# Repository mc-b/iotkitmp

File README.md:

ESP32 DevKitC und IoTKitV3
==========================

| ESP32 DevKitC | IoTKitV3 Shield |
| ---------- | ------ |
|  |  |
| Quelle: [Micropython](https://docs.micropython.org/en/latest/esp32/quickref.html) | Quelle: [IoTKitV3](https://github.com/iotkitv3/intro) |

Beispiele für das [ESP32 DevKitC](https://docs.espressif.com/projects/esp-idf/en/latest/esp32/hw-reference/esp32/get-started-devkitc.html) Board in Kombination mit dem [IoTKit V3 Shield](https://github.com/iotkitv3/iotkit#iotkit-v3-shield-small).

Dieses Repository basiert auf den Erfahrungen mit dem [IoTKitV1 - V3](https://github.com/iotkitv3/intro).

## Grundlagen

* [Hardware](hw/)
* [Software und Installation](sw/)
* [GPIO](gpio)
* [Sensoren](sensors)
* [Aktoren](actors)

## Bus Systeme

* [UART](uart)
* [I²C/TWI](i2c)
* [SPI](spi)

### Internet IoT Protokolle

* [WLAN](wlan/) inkl. Konfiguration SSID und WLAN Password.
* [HTTP und REST](http/) 
* [MQTT](mqtt/)

## Anwendungen / Umsetzungen

* [NFC / RFID](rfid/)
* [Cloud Anbindung](cloud/) an Amazon (AWS) und Microsoft (Azure).
* [Internet of Things – Machine Learning Fast Data Pipeline mit Docker/Kubernetes](pipeline/)

## Kurse und Weiterbildung 

* [CAS Internet of Things (IoT) and Digital Ecosystem Technologien verstehen, Lösungen entwickeln](http://hslu.ch/casiot)
* [CAS Cloud and Platform Manager Mit Cloud-Expertise die Digitalisierung mitgestalten](http://hslu.ch/cascpm) 
* [Internet of Things (IoT) im Einsatz](https://www.digicomp.ch/d/IOTEIN)

## Links

* [Die drei Hauptklassen von IoT](https://www.arm.com/products/iot/soc)
* [Geschäftsmodelle und IoT](https://www.iot-lab.ch/publications/#whitepapers)

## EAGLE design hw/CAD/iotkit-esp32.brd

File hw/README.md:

ESP32-DevKitC
-------------
***

> [⇧ **Home**](../README.md)

- - -

* 32-Bit-MCU und 2,4-GHz-WLAN und Bluetooth/Bluetooth LE
* Eingebetteter ESP32, zwei oder ein Xtensa® 32-Bit-LX6-Mikroprozessor(en) mit einstellbarer Taktfrequenz von 80 MHz bis 240 MHz
* +19,5 dBm Ausgangsleistung sorgen für eine gute physikalische Reichweite
* Klassisches Bluetooth für Legacy-Verbindungen, unterstützt auch L2CAP, SDP, GAP, SMP, AVDTP, AVCTP, A2DP (SNK) und AVRCP (CT)
* Unterstützung für Bluetooth Low Energy (Bluetooth LE)-Profile einschließlich L2CAP, GAP, GATT, SMP und GATT-basierte Profile wie BluFi, SPP-like usw
* Bluetooth Low Energy (Bluetooth LE) stellt eine Verbindung zu Smartphones her und sendet Niedrigenergie-Beacons zur einfachen Erkennung
* Der Ruhestrom beträgt weniger als 5 μA und eignet sich daher für batteriebetriebene und tragbare Elektronikanwendungen
* Zu den Peripheriegeräten gehören kapazitive Berührungssensoren, Hall-Sensor, SD-Kartenschnittstelle, Ethernet, Hochgeschwindigkeits-SPI, UART, I2S und I2C
* Vollständig zertifiziert mit integrierter Antenne und Software-Stacks

### Pins

* 22 Pins In/Out
*  4 Pins nur Input (34, 35, 36, 39)
* max. 8 PWM Channels gleichzeitig

### Links

* [Hersteller](https://www.espressif.com/en/products/modules)
* [Board](https://www.mouser.ch/ProductDetail/356-ESP32-DEVKTC32VE)
* [Firmware](https://micropython.org/download/esp32/) - Version V1.14 verwenden, V1.18 funktioniert PWM nicht.

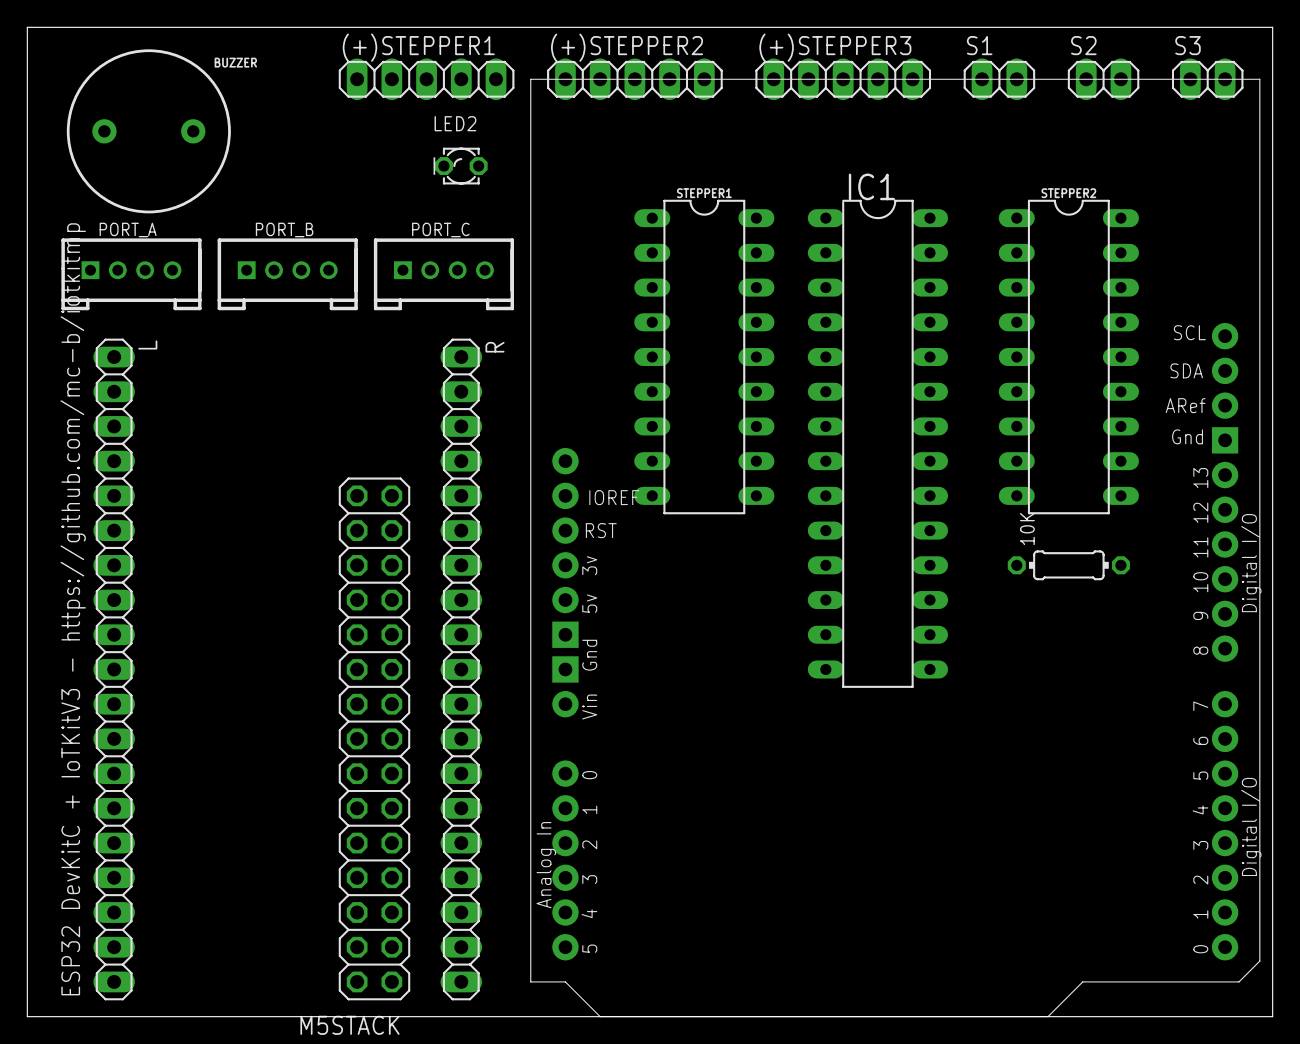
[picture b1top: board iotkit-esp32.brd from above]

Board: 2 copper layers, 91.1 x 72.4 mm, 19 parts (0 on the bottom side), 53 nets, no tracks yet.

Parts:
10K: 0204/7
(+)STEPPER1: PB0-3; 1X05
(+)STEPPER2: PB4-7; 1X05
(+)STEPPER3: PA7-4; 1X05
BUZZER: BUZZER-PTH; BUZZER-12MM
IC1: MCP23017SP 0x20; DIL28-3
L: 1X19
LED2: LED_LD260
M5STACK: 2X15
PORT_A: I2C; HW4-2.0
PORT_B: I2C; HW4-2.0
PORT_C: I2C; HW4-2.0
R: 1X19
S1: PA0; 1X02
S2: PA1; 1X02
S3: PA2; 1X02
STEPPER1, STEPPER2: DIL18
U$1: ARDUINO_LEONARDO

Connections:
3V3: 10K.1, IC1.9, L.1, M5STACK.11, U$1.3V
5V: (+)STEPPER1.1, (+)STEPPER2.1, (+)STEPPER3.1, L.19, M5STACK.27, PORT_A.3, PORT_B.3, PORT_C.3, STEPPER1.10, STEPPER2.10, U$1.5V
A2: L.7, M5STACK.1, U$1.A2
A3: L.8, M5STACK.3, U$1.A3
A4: L.5, M5STACK.13, U$1.A4
A5: L.6, M5STACK.14, U$1.A5
BUZ: BUZZER.+, L.10
D0: M5STACK.16, PORT_C.1, R.5, U$1.D0
D1: M5STACK.15, PORT_C.2, R.4, U$1.D1
D2: L.13, M5STACK.24, U$1.D2
D3: L.15, M5STACK.21, U$1.D3
D4: L.12, M5STACK.23, U$1.D4
D5: R.16, U$1.D5
D6: R.12, U$1.D6
D7: R.11, U$1.D7
D8: M5STACK.9, PORT_B.2, R.9, U$1.D8
D9: M5STACK.22, PORT_B.1, R.8, U$1.D9
D10: L.11, M5STACK.7, U$1.D10
D11: M5STACK.8, R.6, U$1.D11
D12: M5STACK.10, R.3, U$1.D12
D13: M5STACK.12, R.2, U$1.D13
GND: BUZZER.-, IC1.10, IC1.15, IC1.16, IC1.17, L.14, LED2.K, M5STACK.2, M5STACK.4, M5STACK.6, PORT_A.4, PORT_B.4, PORT_C.4, R.1, R.7, S1.2, S2.2, S3.2, STEPPER1.9, STEPPER2.9, U$1.GND, U$1.GND$2, U$1.GND$3
LED1: LED2.A, R.10
unnamed: (+)STEPPER2.2, STEPPER1.14
unnamed: (+)STEPPER2.3, STEPPER1.13
unnamed: (+)STEPPER2.4, STEPPER1.12
unnamed: (+)STEPPER2.5, STEPPER1.11
unnamed: 10K.2, IC1.18
unnamed: (+)STEPPER3.2, STEPPER2.18
unnamed: (+)STEPPER3.3, STEPPER2.17
unnamed: (+)STEPPER3.4, STEPPER2.16
unnamed: (+)STEPPER3.5, STEPPER2.15
unnamed: (+)STEPPER1.2, STEPPER1.18
unnamed: (+)STEPPER1.3, STEPPER1.17
unnamed: (+)STEPPER1.4, STEPPER1.16
unnamed: (+)STEPPER1.5, STEPPER1.15
PA0: IC1.21, S1.1
PA1: IC1.22, S2.1
PA2: IC1.23, S3.1
PA4: IC1.25, STEPPER2.4
PA5: IC1.26, STEPPER2.3
PA6: IC1.27, STEPPER2.2
PA7: IC1.28, STEPPER2.1
PB0: IC1.1, STEPPER1.1
PB1: IC1.2, STEPPER1.2
PB2: IC1.3, STEPPER1.3
PB3: IC1.4, STEPPER1.4
PB4: IC1.5, STEPPER1.5
PB5: IC1.6, STEPPER1.6
PB6: IC1.7, STEPPER1.7
PB7: IC1.8, STEPPER1.8
SCL: IC1.12, M5STACK.19, PORT_A.1, R.13, U$1.SCL
SDA: IC1.13, M5STACK.20, PORT_A.2, R.15, U$1.SDA

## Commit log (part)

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2022-02-13 Grundfunktionen
2022-02-14 Detailkorrekturen
2022-02-14 Standard Library verwenden
2022-02-14 Libraries
2022-02-14 LED und Buzzer
2022-02-14 Konstanten verwenden
2022-02-14 APDS9960 Sensor
2022-02-14 RFID Reader
2022-02-14 LED an Pin 5
2022-02-14 Adapter Board
2022-02-14 Inkl. Stepper
2022-02-14 Stepper an 5V
2022-02-14 Breite ESP32 falsch
2022-02-15 Gerber Version 1.0
2022-02-15 Intro
2022-02-15 Umbau Konfiguration
2022-02-15 GPIO
2022-02-15 Link
2022-02-15 Sensoren
2022-02-15 Aktoren
2022-02-15 UART
2022-02-15 RFID
2022-02-15 Links
2022-02-15 WLAN
2022-02-15 Deutsch
2022-02-16 Bilder
2022-02-16 aktuelle Bild
2022-02-16 HTTP
2022-02-16 Sunrise / Sunset
2022-02-16 ThingSpeak Grundgeruest
2022-02-16 mit urequest
2022-02-16 Umbau auf Sockets
2022-02-20 M5Stack Core2 Erweiterungen
2022-02-20 ohne pro
2022-02-20 M5Stack Adapterplatine
2022-02-21 Fehlende Pins nachgetragen
2022-02-22 Hilfsscript um Firmware zu flaschen - nur Windows mit Git/Bash
2022-02-22 Beschreibung Pin-Belegungen
2022-02-22 Schrittmotor
2022-02-22 Stepper Beispiel
2022-02-22 Alarmsirene
2022-02-22 Umbau auf urequests
2022-02-22 mqtt
2022-02-22 Azure Cloud Beispiel bzw. Link darauf
2022-02-22 Data Pipeline
2022-02-22 pipeline
2022-02-23 Zustaende, Alert, RFID Abhandlung
2022-02-23 Standard MQTT Broker
2022-02-23 Mehr Details
2022-02-23 Detailbeschreibungen
2022-03-03 M5stack Seitenverkehrt korr.
2022-03-03 Fehlerhaft
2022-03-03 M5Stack Spiegelverkehrt korr.
2022-03-23 ESP8266-01 PinOut

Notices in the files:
parts and their libraries:
SparkFun-Electromechanical: Licensing: Creative Commons ShareAlike 4.0 International - https://creativecommons.org/licenses/by-sa/4.0
